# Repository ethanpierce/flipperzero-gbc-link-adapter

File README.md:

# flipperzero-gbc-link-adapter
Flipper Zero GBC Link Adapter in KiCad

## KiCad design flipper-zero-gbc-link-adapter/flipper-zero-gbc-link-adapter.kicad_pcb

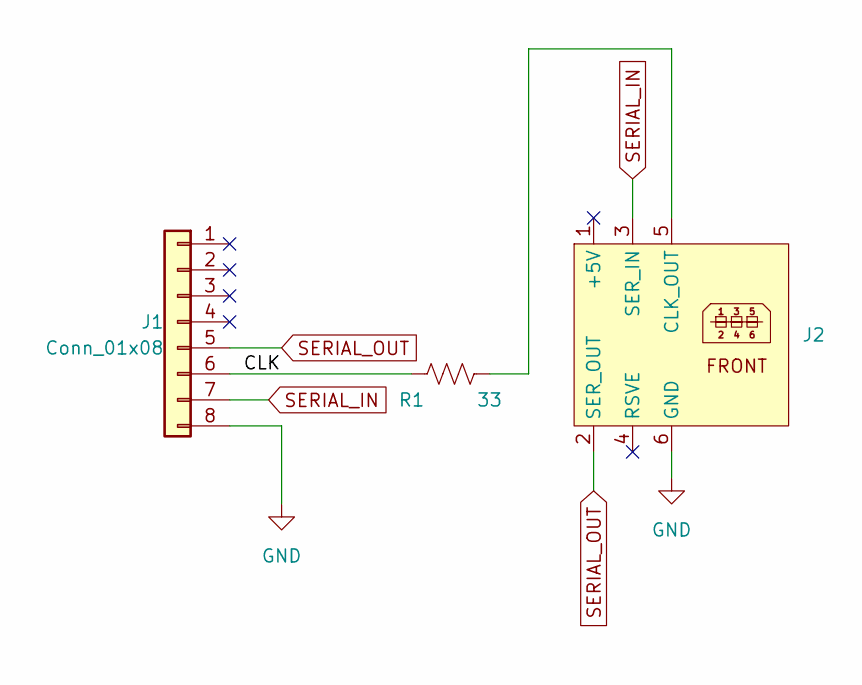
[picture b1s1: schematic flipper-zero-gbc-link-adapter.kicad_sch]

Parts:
J1: Conn_01x08; PinHeader_1x08_P2.54mm_Horizontal
J2: gbc-link-cable-adapter
R1: 33; R_0805_2012Metric_Pad1.20x1.40mm_HandSolder

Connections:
/CLK: J1.6, R1.1
GND: J1.8, J2.6 (GND)
unnamed: J2.5 (CLK_OUT), R1.2
SERIAL_IN: J1.7, J2.3 (SER_IN)
SERIAL_OUT: J1.5, J2.2 (SER_OUT)

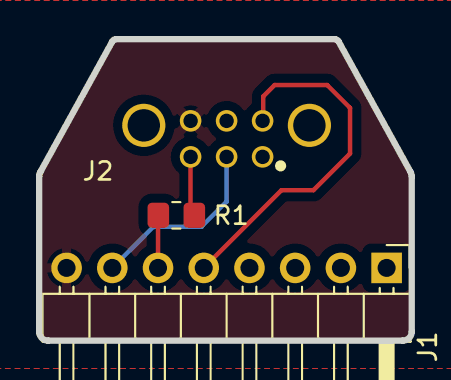
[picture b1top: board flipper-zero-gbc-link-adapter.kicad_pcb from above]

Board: 2 copper layers, 20.7 x 16.7 mm, 3 parts (0 on the bottom side), 5 nets.

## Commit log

2023-10-20 initial prototype release
